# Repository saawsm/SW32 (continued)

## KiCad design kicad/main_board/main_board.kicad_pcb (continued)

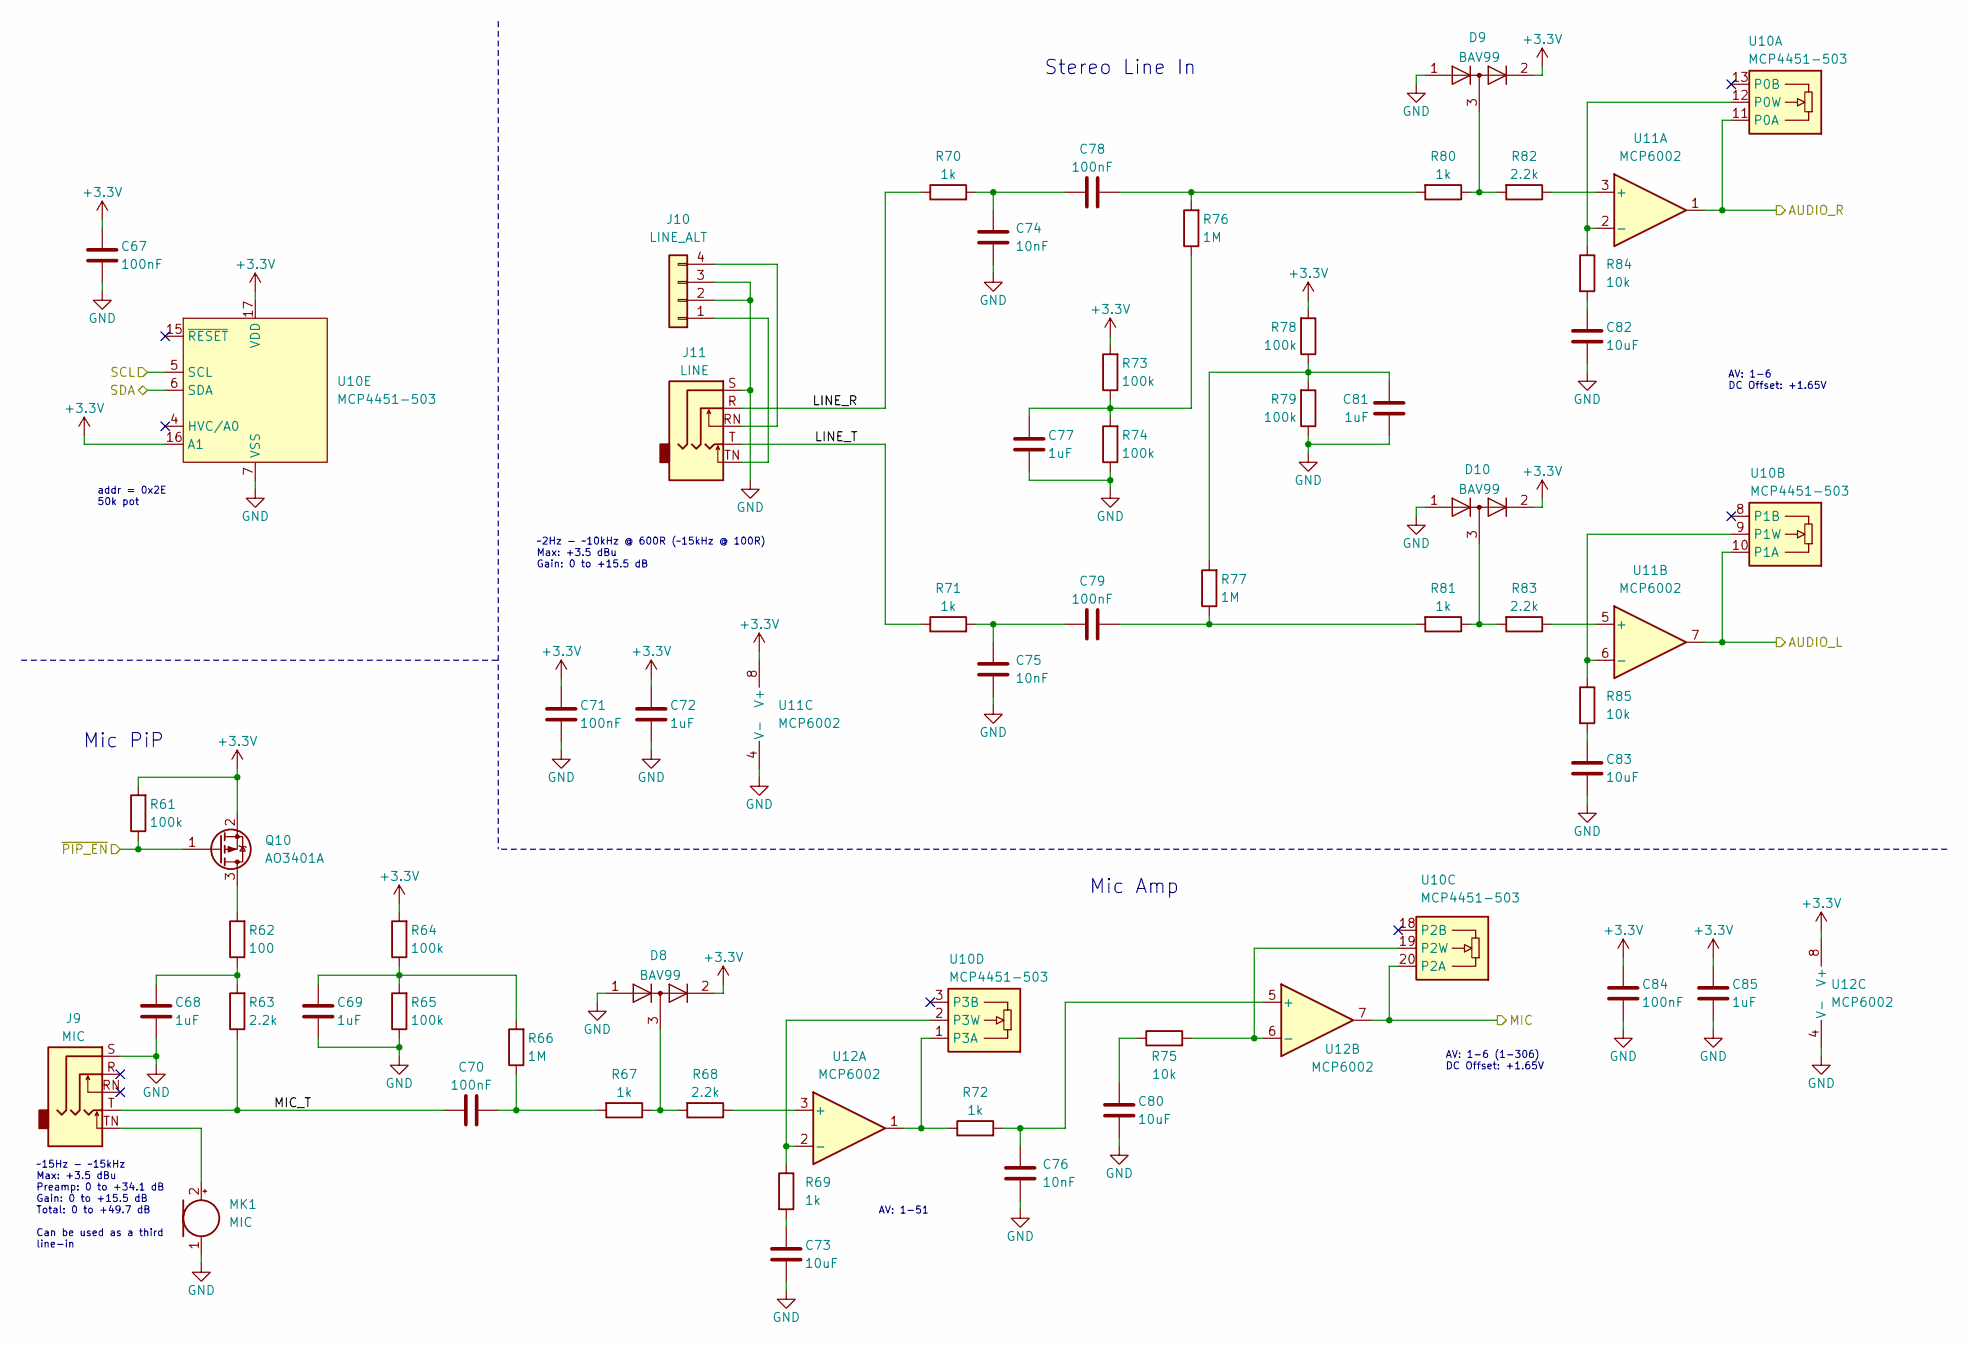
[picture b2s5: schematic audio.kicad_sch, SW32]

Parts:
C67, C70, C71, C78, C79, C84: 100nF; C_0603_1608Metric; LCSC C14663
C68, C69, C72, C77, C81, C85: 1uF; C_0603_1608Metric; LCSC C15849
C73, C80, C82, C83: 10uF; C_0603_1608Metric; LCSC C96446
C74, C75, C76: 10nF; C_0603_1608Metric; LCSC C57112
D8, D9, D10: BAV99; SOT-23; LCSC C2500
J9: MIC; PJ-3062-CO; LCSC C319113
J10: LINE_ALT; PinHeader_1x04_P2.54mm_Vertical; LCSC C2691448
J11: LINE; PJ-3062-CO; LCSC C319113
MK1: MIC; CUI_CMC-4013-SMT; LCSC C5160218
Q10: AO3401A; SOT-23; LCSC C15127
R61, R64, R65, R73, R74, R78, R79: 100k; R_0603_1608Metric; LCSC C25803
R62: 100; R_0603_1608Metric; LCSC C22775
R63, R68, R82, R83: 2.2k; R_0603_1608Metric; LCSC C4190
R66, R76, R77: 1M; R_0603_1608Metric; LCSC C22935
R67, R69, R70, R71, R72, R80, R81: 1k; R_0603_1608Metric; LCSC C21190
R75, R84, R85: 10k; R_0603_1608Metric; LCSC C25804
U10: MCP4451-503; TSSOP-20_4.4x6.5mm_P0.65mm; LCSC C638706
U11, U12: MCP6002; MSOP-8_3x3mm_P0.65mm; LCSC C2652308

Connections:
+3.3V: C67.1, C71.1, C72.1, C84.1, C85.1, D8.2 (A), D9.2 (A), D10.2 (A), Q10.2 (S), R61.2, R64.2, R73.2, R78.2, U10.16 (A1), U10.17 (VDD), U11.8 (V+), U12.8 (V+); also elsewhere on the board
/Audio/AUDIO_L: U10.10 (P1A), U11.7; also elsewhere on the board
/Audio/AUDIO_R: U10.11 (P0A), U11.1; also elsewhere on the board
/Audio/LINE_R: J11.R, R70.1
/Audio/LINE_T: J11.T, R71.1
/Audio/MIC: U10.20 (P2A), U12.7; also elsewhere on the board
/Audio/MIC_T: C70.1, J9.T, R63.1
/Audio/~PIP_EN: Q10.1 (G), R61.1; also elsewhere on the board
/Charger/SCL: U10.5 (SCL); also elsewhere on the board
/Charger/SDA: U10.6 (SDA); also elsewhere on the board
GND: C67.2, C68.2, C69.2, C71.2, C72.2, C73.2, C74.2, C75.2, C76.2, C77.2, C80.2, C81.2, C82.2, C83.2, C84.2, C85.2, D8.1 (K), D9.1 (K), D10.1 (K), J9.S, J10.2, J10.3, J11.S, MK1.1 (-), R65.1, R74.1, R79.1, U10.7 (VSS), U11.4 (V-), U12.4 (V-); also elsewhere on the board
unnamed: C68.1, R62.1, R63.2
unnamed: C69.1, R64.1, R65.2, R66.2
unnamed: C70.2, R66.1, R67.2
unnamed: C73.1, R69.2
unnamed: C74.1, C78.1, R70.2
unnamed: C75.1, C79.1, R71.2
unnamed: C77.1, R73.1, R74.2, R76.1
unnamed: C78.2, R76.2, R80.2
unnamed: C79.2, R77.1, R81.2
unnamed: C80.1, R75.1
unnamed: C81.1, R77.2, R78.1, R79.2
unnamed: C82.1, R84.2
unnamed: C83.1, R85.2
unnamed: D8.3 (K), R67.1, R68.2
unnamed: D9.3 (K), R80.1, R82.2
unnamed: D10.3 (K), R81.1, R83.2
unnamed: J10.1, J11.TN
unnamed: J10.4, J11.RN
unnamed: J9.TN, MK1.2 (+)
unnamed: Q10.3 (D), R62.2
unnamed: R84.1, U10.12 (P0W), U11.2 (-)
unnamed: R85.1, U10.9 (P1W), U11.6 (-)
unnamed: R75.2, U10.19 (P2W), U12.6 (-)
unnamed: R72.1, U10.1 (P3A), U12.1
unnamed: R69.1, U10.2 (P3W), U12.2 (-)
unnamed: R82.1, U11.3 (+)
unnamed: R83.1, U11.5 (+)
unnamed: R68.1, U12.3 (+)
unnamed: C76.1, R72.2, U12.5 (+)

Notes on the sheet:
AV: 1-6 (1-306) DC Offset: +1.65V
Mic PiP
Stereo Line In
~2Hz - ~10kHz @ 600R (~15kHz @ 100R) Max: +3.5 dBu Gain: 0 to +15.5 dB
addr = 0x2E 50k pot
Mic Amp
~15Hz - ~15kHz Max: +3.5 dBu Preamp: 0 to +34.1 dB Gain: 0 to +15.5 dB Total: 0 to +49.7 dB Can be used as a third line-in
AV: 1-51
AV: 1-6 DC Offset: +1.65V

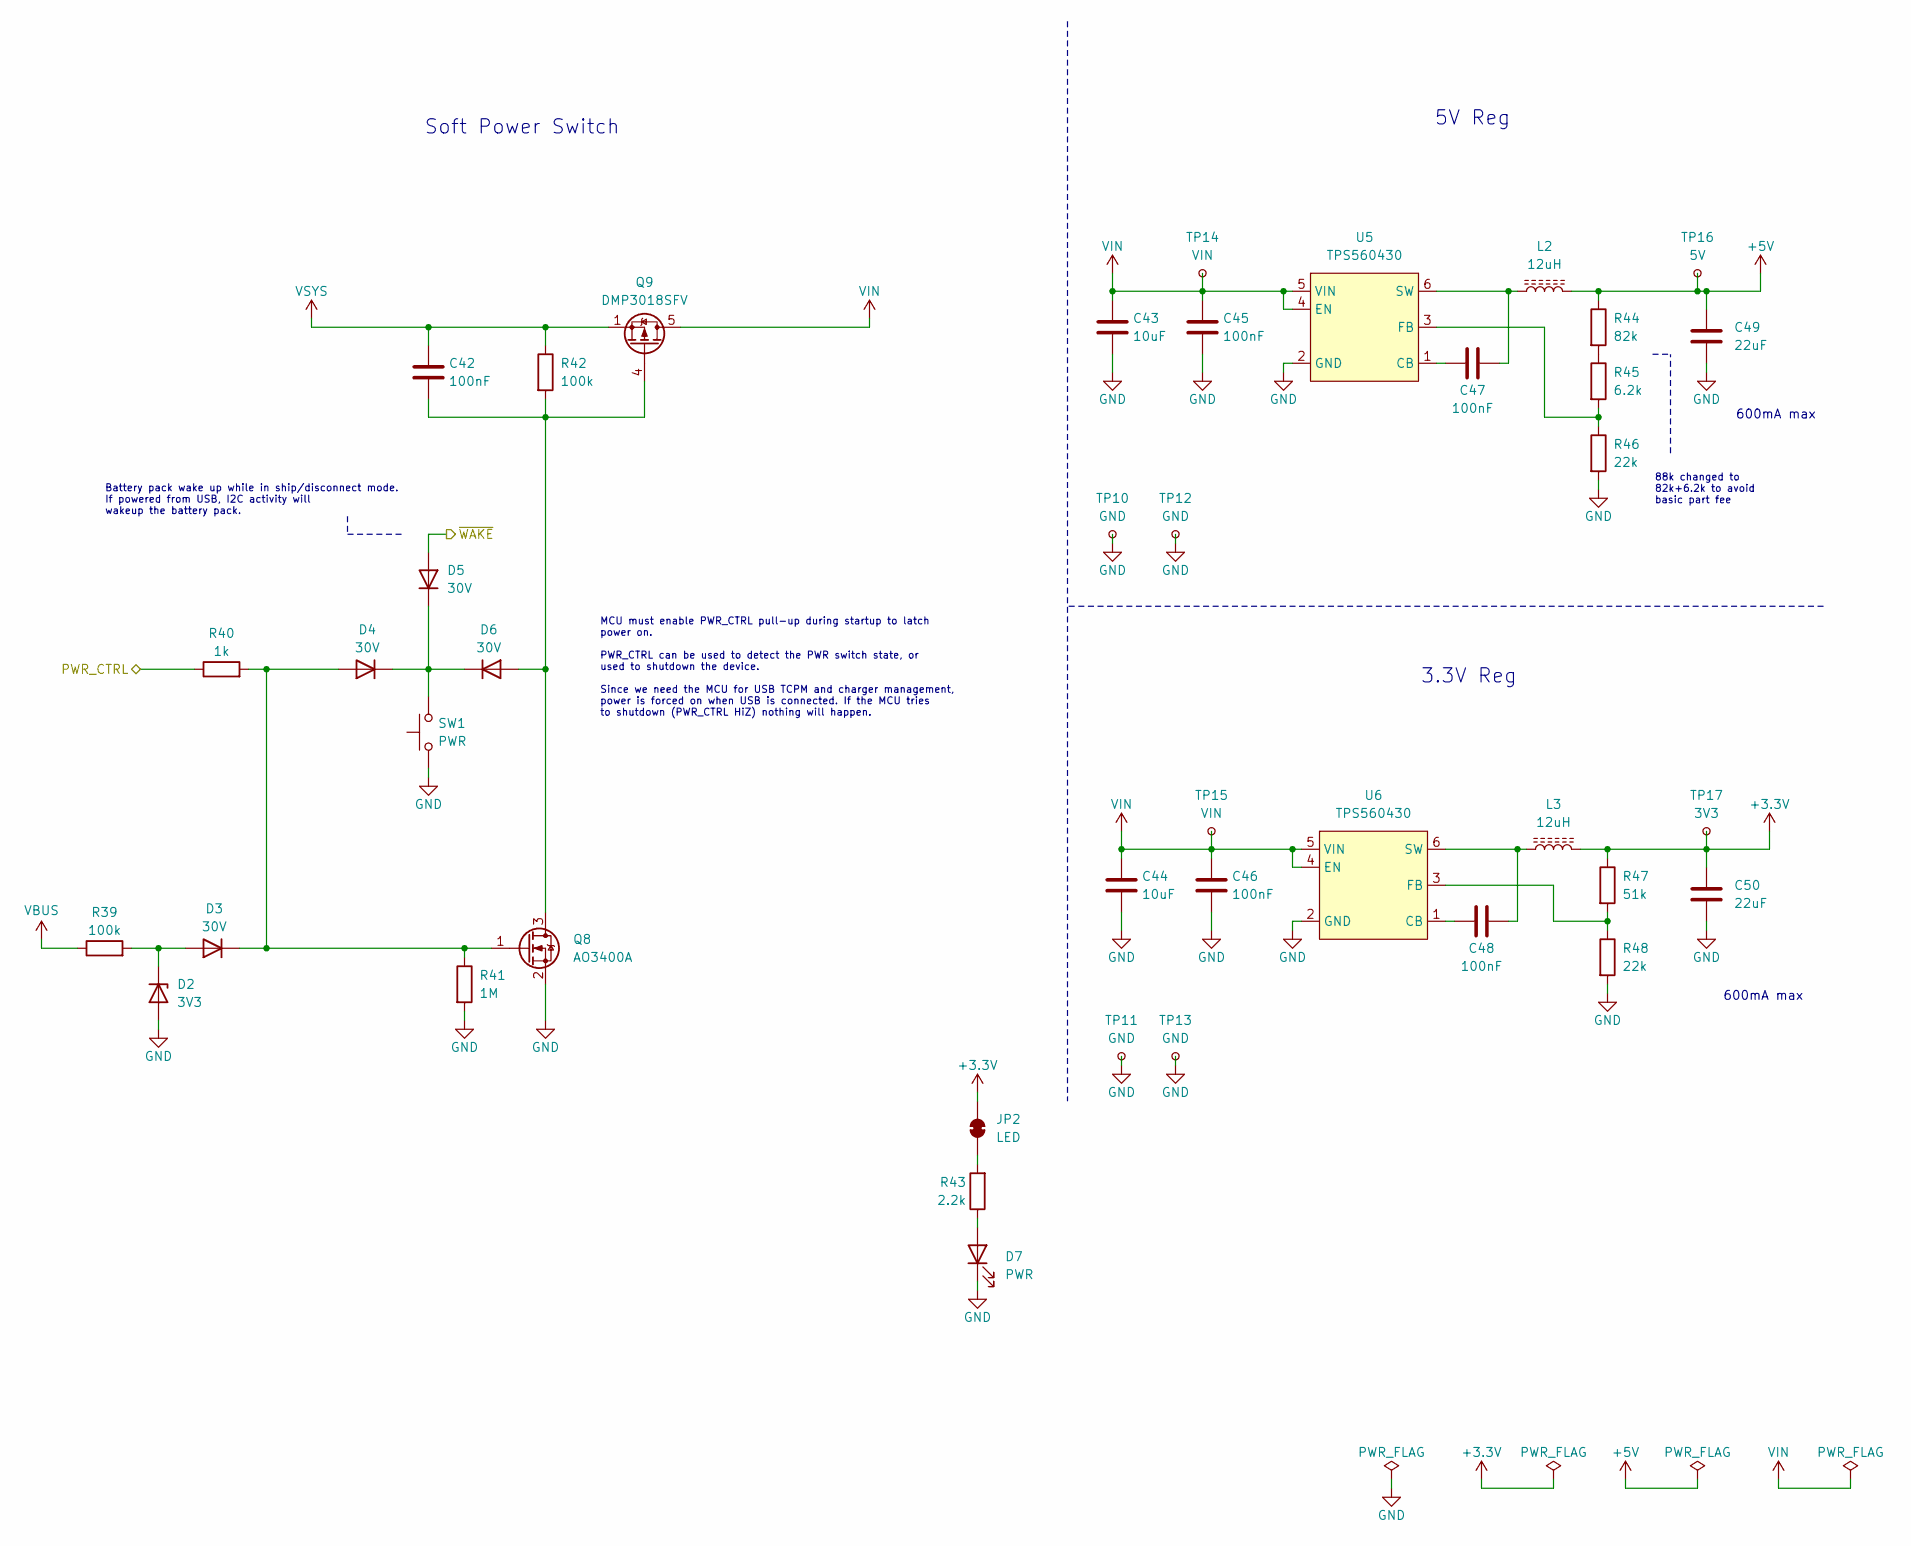
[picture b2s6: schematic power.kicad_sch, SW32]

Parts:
C42, C45, C46, C47, C48: 100nF; C_0603_1608Metric; LCSC C14663
C43, C44: 10uF; C_0805_2012Metric; LCSC C440198
C49, C50: 22uF; C_0805_2012Metric; LCSC C45783
D2: 3V3; D_SOD-323; LCSC C391441
D3, D4, D5, D6: 30V; D_SOD-323; LCSC C2128
D7: PWR; LED_0603_1608Metric; LCSC C2286
JP2: LED; SolderJumper-2_P1.3mm_Bridged_RoundedPad1.0x1.5mm
L2, L3: 12uH; L_Sunlord_SWPA6020S; LCSC C96927
Q8: AO3400A; SOT-23; LCSC C20917
Q9: DMP3018SFV; Diodes_PowerDI3333-8_ThermalVias; LCSC C461075
R39, R42: 100k; R_0603_1608Metric; LCSC C25803
R40: 1k; R_0603_1608Metric; LCSC C21190
R41: 1M; R_0603_1608Metric; LCSC C22935
R43: 2.2k; R_0603_1608Metric; LCSC C4190
R44: 82k; R_0603_1608Metric; LCSC C23254
R45: 6.2k; R_0603_1608Metric; LCSC C4260
R46, R48: 22k; R_0603_1608Metric; LCSC C31850
R47: 51k; R_0603_1608Metric; LCSC C23196
SW1: PWR; SW_Tactile_SPST_Angled_PTS645Vx31-2LFS; LCSC C2804591
TP10, TP11, TP12, TP13: GND; TestPoint_Pad_D1.0mm
TP14, TP15: VIN; TestPoint_Pad_D1.0mm
TP16: 5V; TestPoint_Pad_D1.0mm
TP17: 3V3; TestPoint_Pad_D1.0mm
U5, U6: TPS560430; SOT-23-6; LCSC C524782

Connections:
+3.3V: C50.2, JP2.1 (A), L3.2, R47.1, TP17.1; also elsewhere on the board
+5V: C49.2, L2.2, R44.1, TP16.1; also elsewhere on the board
/Charger/~WAKE: D5.2 (A); also elsewhere on the board
/Controller/PWR_CTRL: R40.1; also elsewhere on the board
GND: C43.1, C44.1, C45.1, C46.1, C49.1, C50.1, D2.2 (A), D7.1 (K), Q8.2 (S), R41.2, R46.2, R48.2, SW1.1, TP10.1, TP11.1, TP12.1, TP13.1, U5.2 (GND), U6.2 (GND); also elsewhere on the board
unnamed: D2.1 (K), D3.2 (A), R39.2
unnamed: D3.1 (K), D4.2 (A), Q8.1 (G), R40.2, R41.1
unnamed: D4.1 (K), D5.1 (K), D6.1 (K), SW1.2
unnamed: C42.1, D6.2 (A), Q8.3 (D), Q9.4 (G), R42.2
unnamed: D7.2 (A), R43.1
unnamed: JP2.2 (B), R43.2
unnamed: R44.2, R45.1
unnamed: C47.1, U5.1 (CB)
unnamed: R45.2, R46.1, U5.3 (FB)
unnamed: C47.2, L2.1, U5.6 (SW)
unnamed: C48.1, U6.1 (CB)
unnamed: R47.2, R48.1, U6.3 (FB)
unnamed: C48.2, L3.1, U6.6 (SW)
VBUS: R39.1; also elsewhere on the board
VIN: C43.2, C44.2, C45.2, C46.2, Q9.5 (D), TP14.1, TP15.1, U5.4 (EN), U5.5 (VIN), U6.4 (EN), U6.5 (VIN); also elsewhere on the board
VSYS: C42.2, Q9.1 (S), Q9.2 (S), Q9.3 (S), R42.1; also elsewhere on the board

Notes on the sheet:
88k changed to 82k+6.2k to avoid basic part fee
600mA max
5V Reg
3.3V Reg
Soft Power Switch
Battery pack wake up while in ship/disconnect mode. If powered from USB, I2C activity will wakeup the battery pack.
MCU must enable PWR_CTRL pull-up during startup to latch power on. PWR_CTRL can be used to detect the PWR switch state, or used to shutdown the device. Since we need the MCU for USB TCPM and charger management, power is forced on when USB is connected. If the MCU tries to shutdown (PWR_CTRL HiZ) no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

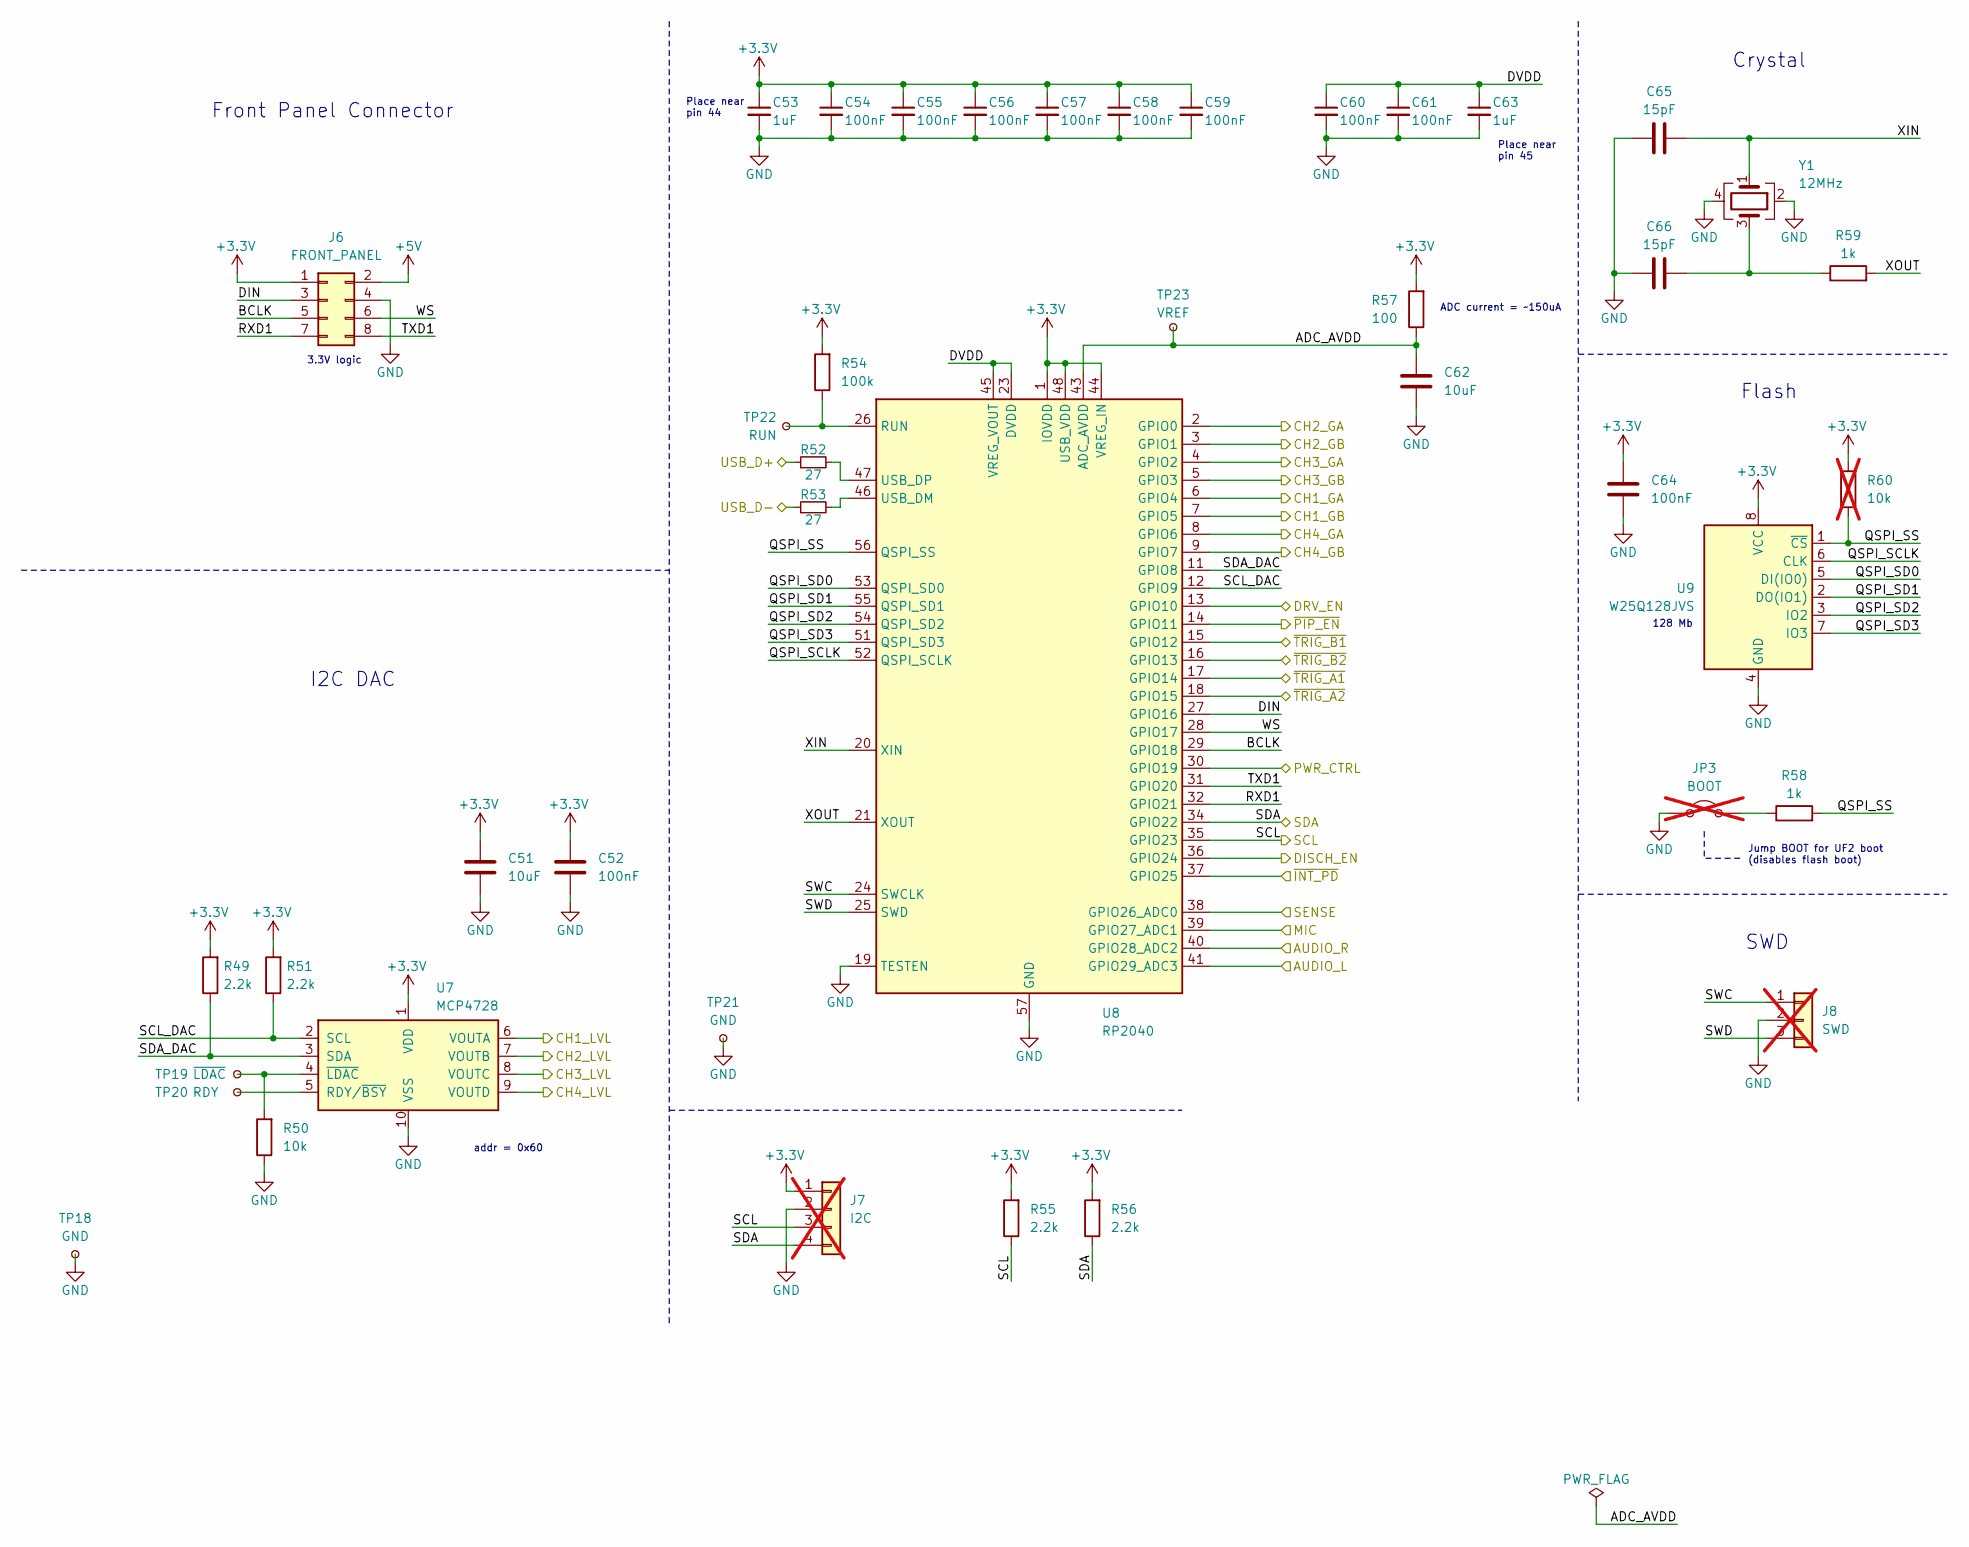
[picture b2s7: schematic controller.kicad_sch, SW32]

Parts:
C51, C62: 10uF; C_0603_1608Metric; LCSC C96446
C52, C64: 100nF; C_0603_1608Metric; LCSC C14663
C53, C63: 1uF; C_0603_1608Metric; LCSC C15849
C54, C55, C56, C57, C58, C59, C60, C61: 100nF; C_0402_1005Metric; LCSC C307331
C65, C66: 15pF; C_0402_1005Metric; LCSC C1548
J6: FRONT_PANEL; IDC-Header_2x04_P2.54mm_Vertical; LCSC C5372864
J7: I2C; PinHeader_1x04_P2.54mm_Vertical; LCSC C2691448; not fitted
J8: SWD; PinHeader_1x03_P2.54mm_Vertical; LCSC C2937625; not fitted
JP3: BOOT; PinHeader_1x02_P2.54mm_Vertical; LCSC C492401; not fitted
R49, R51, R55, R56: 2.2k; R_0603_1608Metric; LCSC C4190
R50: 10k; R_0603_1608Metric; LCSC C25804
R52, R53: 27; R_0402_1005Metric; LCSC C25100
R54: 100k; R_0603_1608Metric; LCSC C25803
R57: 100; R_0603_1608Metric; LCSC C22775
R58: 1k; R_0603_1608Metric; LCSC C21190
R59: 1k; R_0402_1005Metric; LCSC C11702
R60: 10k; R_0603_1608Metric; LCSC C25804; not fitted
TP18, TP21: GND; TestPoint_Pad_D1.0mm
TP19: ~{LDAC}; TestPoint_Pad_D1.0mm
TP20: RDY; TestPoint_Pad_D1.0mm
TP22: RUN; TestPoint_Pad_D1.0mm
TP23: VREF; TestPoint_Pad_D1.0mm
U7: MCP4728; MSOP-10_3x3mm_P0.5mm; LCSC C108207
U8: RP2040; QFN-56-1EP_7x7mm_P0.4mm_EP3.2x3.2mm_ThermalVias; LCSC C2040
U9: W25Q128JVS; SOIC-8_5.23x5.23mm_P1.27mm; LCSC C97521
Y1: 12MHz; Crystal_SMD_3225-4Pin_3.2x2.5mm; LCSC C20625731

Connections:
+3.3V: C51.1, C52.1, C53.1, C54.1, C55.1, C56.1, C57.1, C58.1, C59.1, C64.1, J6.1, J7.1, R49.2, R51.2, R54.2, R55.2, R56.2, R57.2, R60.2, U7.1 (VDD), U8.1 (IOVDD), U8.10 (IOVDD), U8.22 (IOVDD), U8.33 (IOVDD), U8.42 (IOVDD), U8.44 (VREG_IN), U8.48 (USB_VDD), U8.49 (IOVDD), U9.8 (VCC); also elsewhere on the board
+5V: J6.2; also elsewhere on the board
/Audio/AUDIO_L: U8.41 (GPIO29_ADC3); also elsewhere on the board
/Audio/AUDIO_R: U8.40 (GPIO28_ADC2); also elsewhere on the board
/Audio/MIC: U8.39 (GPIO27_ADC1); also elsewhere on the board
/Audio/~PIP_EN: U8.14 (GPIO11); also elsewhere on the board
/Charger/SCL: J7.3, R55.1, U8.35 (GPIO23); also elsewhere on the board
/Charger/SDA: J7.4, R56.1, U8.34 (GPIO22); also elsewhere on the board
/Controller/ADC_AVDD: C62.1, R57.1, TP23.1, U8.43 (ADC_AVDD)
/Controller/BCLK: J6.5, U8.29 (GPIO18)
/Controller/CH1_GA: U8.6 (GPIO4); also elsewhere on the board
/Controller/CH1_GB: U8.7 (GPIO5); also elsewhere on the board
/Controller/CH1_LVL: U7.6 (VOUTA); also elsewhere on the board
/Controller/CH2_GA: U8.2 (GPIO0); also elsewhere on the board
/Controller/CH2_GB: U8.3 (GPIO1); also elsewhere on the board
/Controller/CH2_LVL: U7.7 (VOUTB); also elsewhere on the board
/Controller/CH3_GA: U8.4 (GPIO2); also elsewhere on the board
/Controller/CH3_GB: U8.5 (GPIO3); also elsewhere on the board
/Controller/CH3_LVL: U7.8 (VOUTC); also elsewhere on the board
/Controller/CH4_GA: U8.8 (GPIO6); also elsewhere on the board
/Controller/CH4_GB: U8.9 (GPIO7); also elsewhere on the board
/Controller/CH4_LVL: U7.9 (VOUTD); also elsewhere on the board
/Controller/DIN: J6.3, U8.27 (GPIO16)
/Controller/DISCH_EN: U8.36 (GPIO24); also elsewhere on the board
/Controller/DRV_EN: U8.13 (GPIO10); also elsewhere on the board
/Controller/DVDD: C60.1, C61.1, C63.1, U8.23 (DVDD), U8.45 (VREG_VOUT), U8.50 (DVDD)
/Controller/PWR_CTRL: U8.30 (GPIO19); also elsewhere on the board
/Controller/QSPI_SCLK: U8.52 (QSPI_SCLK), U9.6 (CLK)
/Controller/QSPI_SD0: U8.53 (QSPI_SD0), U9.5 (DI(IO0))
/Controller/QSPI_SD1: U8.55 (QSPI_SD1), U9.2 (DO(IO1))
/Controller/QSPI_SD2: U8.54 (QSPI_SD2), U9.3 (IO2)
/Controller/QSPI_SD3: U8.51 (QSPI_SD3), U9.7 (IO3)
/Controller/QSPI_SS: R58.2, R60.1, U8.56 (QSPI_SS), U9.1 (~CS)
/Controller/RXD1: J6.7, U8.32 (GPIO21)
/Controller/SCL_DAC: R51.1, U7.2 (SCL), U8.12 (GPIO9)
/Controller/SDA_DAC: R49.1, U7.3 (SDA), U8.11 (GPIO8)
/Controller/SENSE: U8.38 (GPIO26_ADC0); also elsewhere on the board
/Controller/SWC: J8.1, U8.24 (SWCLK)
/Controller/SWD: J8.3, U8.25 (SWD)
/Controller/TXD1: J6.8, U8.31 (GPIO20)
/Controller/WS: J6.6, U8.28 (GPIO17)
/Controller/XIN: C65.2, U8.20 (XIN), Y1.1
/Controller/XOUT: R59.2, U8.21 (XOUT)
/Controller/~INT_PD: U8.37 (GPIO25); also elsewhere on the board
/Controller/~TRIG_A1: U8.17 (GPIO14); also elsewhere on the board
/Controller/~TRIG_A2: U8.18 (GPIO15); also elsewhere on the board
/Controller/~TRIG_B1: U8.15 (GPIO12); also elsewhere on the board
/Controller/~TRIG_B2: U8.16 (GPIO13); also elsewhere on the board
/Input/USB_D+: R52.1; also elsewhere on the board
/Input/USB_D-: R53.1; also elsewhere on the board
GND: C51.2, C52.2, C53.2, C54.2, C55.2, C56.2, C57.2, C58.2, C59.2, C60.2, C61.2, C62.2, C63.2, C64.2, C65.1, C66.1, J6.4, J7.2, J8.2, JP3.1 (A), R50.1, TP18.1, TP21.1, U7.10 (VSS), U8.19 (TESTEN), U8.57 (GND), U9.4 (GND), Y1.2, Y1.4; also elsewhere on the board
unnamed: C66.2, R59.1, Y1.3
unnamed: JP3.2 (B), R58.1
unnamed: TP20.1, U7.5 (RDY/~BSY)
unnamed: R50.2, TP19.1, U7.4 (~LDAC)
unnamed: R54.1, TP22.1, U8.26 (RUN)
unnamed: R53.2, U8.46 (USB_DM)
unnamed: R52.2, U8.47 (USB_DP)

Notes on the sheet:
Crystal
Jump BOOT for UF2 boot (disables flash boot)
addr = 0x60
SWD
ADC current = ~150uA
3.3V logic
Front Panel Connector
I2C DAC
Place near pin 44
Place near pin 45
Flash
128 Mb

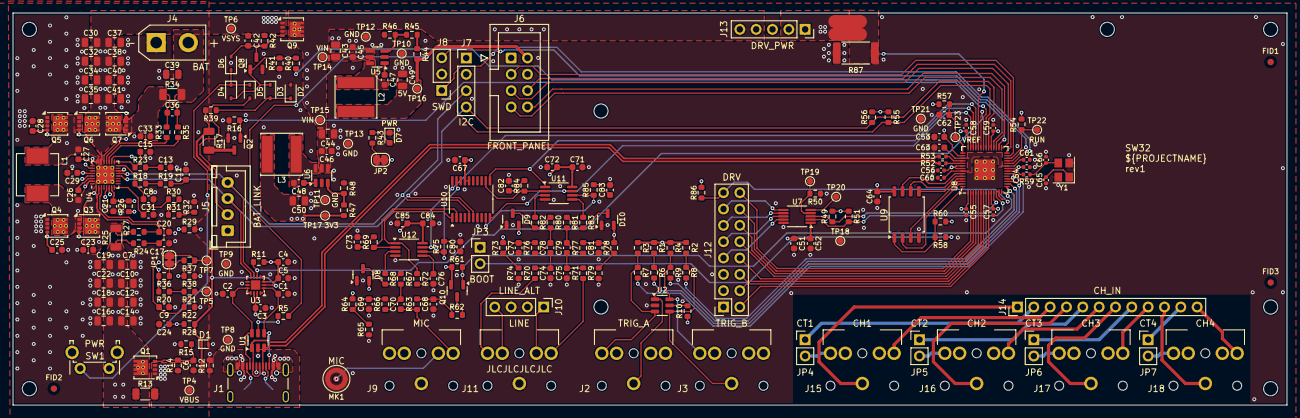
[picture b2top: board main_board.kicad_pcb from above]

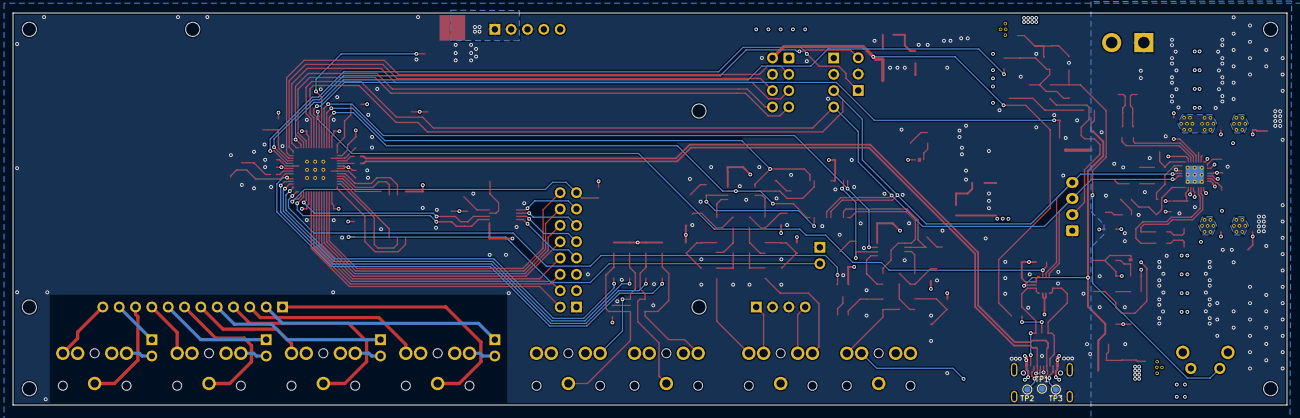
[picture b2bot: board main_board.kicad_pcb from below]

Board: 4 copper layers, 198.1 x 61.0 mm, 271 parts (3 on the bottom side), 169 nets.

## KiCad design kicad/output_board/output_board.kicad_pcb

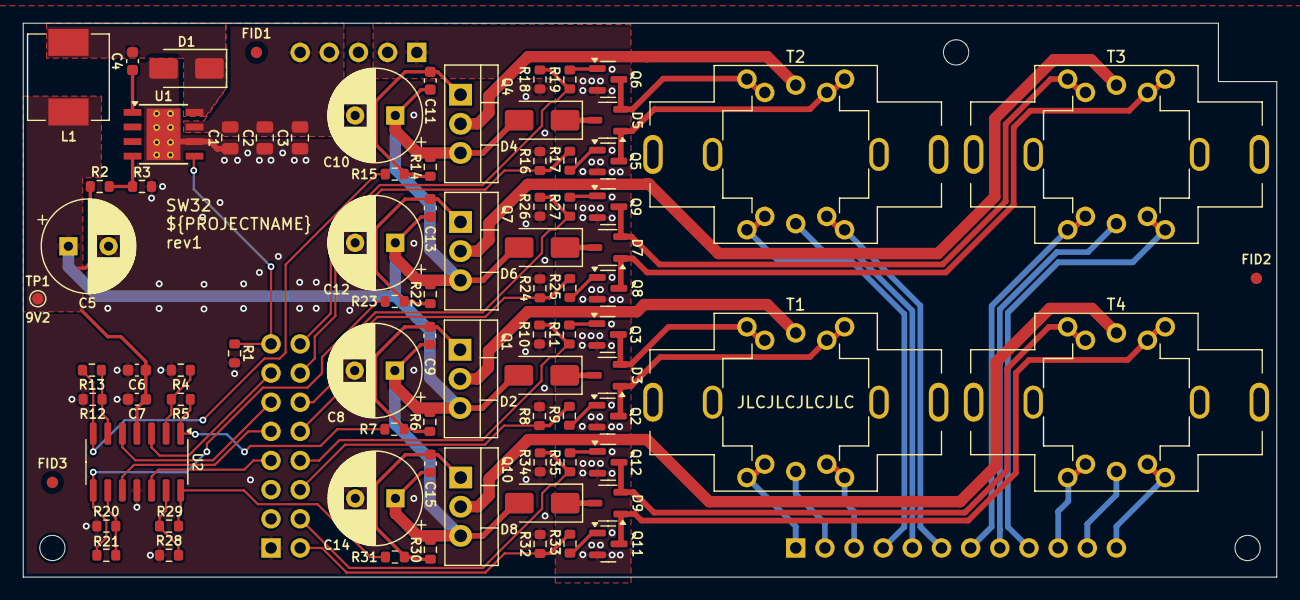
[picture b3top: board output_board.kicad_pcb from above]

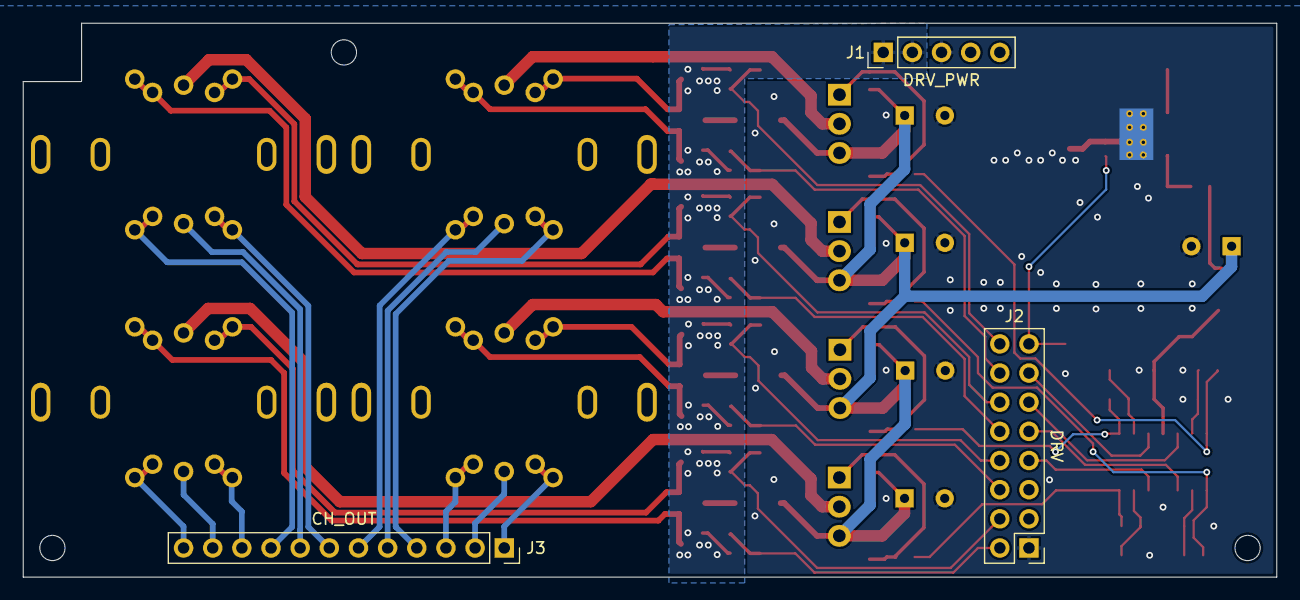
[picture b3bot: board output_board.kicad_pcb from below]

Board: 2 copper layers, 109.2 x 48.3 mm, 88 parts (3 on the bottom side), 68 nets.

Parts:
C1, C2, C3: 22uF; C_0805_2012Metric
C4: 10nF; C_0603_1608Metric
C5, C8, C10, C12, C14: 220uF; CP_Radial_D8.0mm_P3.50mm
C6: 1uF; C_0603_1608Metric
C7, C9, C11, C13, C15: 100nF; C_0603_1608Metric
D1: SS34; D_SMA
D2, D4, D6, D8: SMAJ13A; D_SMA
D3, D5, D7, D9: BAV23CL; SOT-23-3
FID1, FID2, FID3: Fiducial; Fiducial_1mm_Mask2mm
H1, H2, H3: MountingHole; MountingHole_2.2mm_M2
J1: DRV_PWR; PinHeader_1x05_P2.54mm_Vertical
J2: DRV; PinHeader_2x08_P2.54mm_Vertical
J3: CH_OUT; PinSocket_1x12_P2.54mm_Vertical
L1: 15uH; L_CJIANG_FXL0630
Q1, Q4, Q7, Q10: IRF9Z24NPBF; TO-220-3_Vertical
Q2, Q3, Q5, Q6, Q8, Q9, Q11, Q12: AO3400A; SOT-23
R1, R8, R10, R16, R18, R24, R26, R32, R34: 100k; R_0603_1608Metric
R2, R4, R5, R12, R13, R20, R21, R28, R29: 10k; R_0603_1608Metric
R3: 1.5k; R_0603_1608Metric
R6, R14, R22, R30: 2k; R_0603_1608Metric
R7, R15, R23, R31: 1k; R_0603_1608Metric
R9, R11, R17, R19, R25, R27, R33, R35: 100; R_0603_1608Metric
T1, T2, T3, T4: 42TL004/42TU200; 42TL_TU
TP1: 9V2; TestPoint_Pad_D1.0mm
U1: TPS5430DDA; TI_SO-PowerPAD-8_ThermalVias
U2: LM324DT; SOIC-14_3.9x8.7mm_P1.27mm

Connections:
+9V: C5.1, C6.1, C7.1, C8.1, C9.1, C10.1, C11.1, C12.1, C13.1, C14.1, C15.1, D2.2 (A2), D4.2 (A2), D6.2 (A2), D8.2 (A2), L1.2, Q1.3 (S), Q4.3 (S), Q7.3 (S), Q10.3 (S), R2.2, R6.2, R14.2, R22.2, R30.2, TP1.1, U2.4 (V+)
/CH1_GA: J2.8, R10.1, R11.1
/CH1_GB: J2.6, R8.1, R9.1
/CH1_LVL: J2.13, U2.3 (+)
/CH2_GA: J2.16, R18.1, R19.1
/CH2_GB: J2.14, R16.1, R17.1
/CH2_LVL: J2.11, U2.5 (+)
/CH3_GA: J2.12, R26.1, R27.1
/CH3_GB: J2.10, R24.1, R25.1
/CH3_LVL: J2.9, U2.10 (+)
/CH4_GA: J2.4, R34.1, R35.1
/CH4_GB: J2.2, R32.1, R33.1
/CH4_LVL: J2.7, U2.12 (+)
/Channel 1/OUTA: J3.1, T1.4 (S1)
/Channel 1/OUTB: J3.3, T1.6 (S2)
/Channel 1/OUTM: J3.2, T1.5 (SM)
/Channel 2/OUTA: J3.4, T2.4 (S1)
/Channel 2/OUTB: J3.6, T2.6 (S2)
/Channel 2/OUTM: J3.5, T2.5 (SM)
/Channel 3/OUTA: J3.7, T3.4 (S1)
/Channel 3/OUTB: J3.9, T3.6 (S2)
/Channel 3/OUTM: J3.8, T3.5 (SM)
/Channel 4/OUTA: J3.10, T4.4 (S1)
/Channel 4/OUTB: J3.12, T4.6 (S2)
/Channel 4/OUTM: J3.11, T4.5 (SM)
/DRV_EN: J2.15, R1.1, U1.5 (EN)
/PGND: J1.1, J1.2, Q2.2 (S), Q3.2 (S), Q5.2 (S), Q6.2 (S), Q8.2 (S), Q9.2 (S), Q11.2 (S), Q12.2 (S)
GND: C1.1, C2.1, C3.1, C5.2, C6.2, C7.2, C8.2, C10.2, C12.2, C14.2, D1.2 (A), J1.3, J2.1, R1.2, R3.2, R4.1, R8.2, R10.2, R12.1, R16.2, R18.2, R20.1, R24.2, R26.2, R28.1, R32.2, R34.2, U1.6 (GND), U1.9 (GNDPAD), U2.11 (V-)
unnamed: C4.2, D1.1 (K), L1.1, U1.8 (PH)
unnamed: D2.1 (A1), D3.3 (K)
unnamed: D3.1 (A), Q2.3 (D), T1.1 (PR1)
unnamed: D4.1 (A1), D5.3 (K)
unnamed: D5.1 (A), Q5.3 (D), T2.1 (PR1)
unnamed: D6.1 (A1), D7.3 (K)
unnamed: D7.1 (A), Q8.3 (D), T3.1 (PR1)
unnamed: D8.1 (A1), D9.3 (K)
unnamed: D9.1 (A), Q11.3 (D), T4.1 (PR1)
unnamed: Q1.2 (D), T1.2 (PM)
unnamed: C9.2, Q1.1 (G), R6.1, R7.2
unnamed: Q2.1 (G), R9.2
unnamed: D3.2 (K), Q3.3 (D), T1.3 (PR2)
unnamed: Q3.1 (G), R11.2
unnamed: Q4.2 (D), T2.2 (PM)
unnamed: C11.2, Q4.1 (G), R14.1, R15.2
unnamed: Q5.1 (G), R17.2
unnamed: D5.2 (K), Q6.3 (D), T2.3 (PR2)
unnamed: Q6.1 (G), R19.2
unnamed: Q7.2 (D), T3.2 (PM)
unnamed: C13.2, Q7.1 (G), R22.1, R23.2
unnamed: Q8.1 (G), R25.2
unnamed: D7.2 (K), Q9.3 (D), T3.3 (PR2)
unnamed: Q9.1 (G), R27.2
unnamed: Q10.2 (D), T4.2 (PM)
unnamed: C15.2, Q10.1 (G), R30.1, R31.2
unnamed: Q11.1 (G), R33.2
unnamed: D9.2 (K), Q12.3 (D), T4.3 (PR2)
unnamed: Q12.1 (G), R35.2
unnamed: R5.1, R7.1, U2.1
unnamed: R13.1, R15.1, U2.7
unnamed: R21.1, R23.1, U2.8
unnamed: R29.1, R31.1, U2.14
unnamed: C4.1, U1.1 (BOOT)
unnamed: R2.1, R3.1, U1.4 (VSENSE)
unnamed: R4.2, R5.2, U2.2 (-)
unnamed: R12.2, R13.2, U2.6 (-)
unnamed: R20.2, R21.2, U2.9 (-)
unnamed: R28.2, R29.2, U2.13 (-)
VIN: C1.2, C2.2, C3.2, J1.4, J1.5, U1.7 (VIN)

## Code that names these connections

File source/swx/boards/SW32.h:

/*
 * swx
 * Copyright (C) 2024 saawsm
 *
 * This program is free software: you can redistribute it and/or modify
 * it under the terms of the GNU General Public License as published by
 * the Free Software Foundation, either version 3 of the License, or
 * (at your option) any later version.
 *
 * This program is distributed in the hope that it will be useful,
 * but WITHOUT ANY WARRANTY; without even the implied warranty of
 * MERCHANTABILITY or FITNESS FOR A PARTICULAR PURPOSE. See the
 * GNU General Public License for more details.
 *
 * You should have received a copy of the GNU General Public License
 * along with this program.  If not, see <http://www.gnu.org/licenses/>.
 */

#ifndef _BOARDS_SW32_H
#define _BOARDS_SW32_H

#define PIN_PWR_CTRL (19)
#define PIN_DRV_EN (10)
#define PIN_PIP_EN (11) // active low
#define PIN_DISCH_EN (24)

#define PIN_INT_PD (25) // active low

// -------- Triggers --------
#define PIN_TRIG_A1 (14) // active low
#define PIN_TRIG_A2 (15) // active low
#define PIN_TRIG_B1 (12) // active low
#define PIN_TRIG_B2 (13) // active low

// -------- I2C --------
#define PIN_I2C_SCL (23)
#define PIN_I2C_SDA (22)
#define I2C_PORT (i2c1)
#define I2C_FREQ (400000) // Hz

#define PIN_I2C_SCL_DAC (9)
#define PIN_I2C_SDA_DAC (8)
#define I2C_PORT_DAC (i2c0)
#define I2C_FREQ_DAC (400000) // Hz

#define I2C_ADDRESS_DAC (0x60)
#define I2C_ADDRESS_POT (0x2F)

// -------- UART --------
#define PIN_TXD1 (20)
#define PIN_RXD1 (21)

#define UART_PORT (uart1)
#define UART_BAUD (115200)

// -------- I2S Audio --------
#define PIN_I2S_DIN (16)
#define PIN_I2S_WS (17)
#define PIN_I2S_BCLK (18)

// -------- ADC --------
#define PIN_ADC_SENSE (26)
#define PIN_ADC_AUDIO_LEFT (29)
#define PIN_ADC_AUDIO_RIGHT (28)
#define PIN_ADC_AUDIO_MIC (27)

// -------- Channels --------

// -------- Channel Defaults --------

#define CH_CAL_THRESHOLD_OK (0.015f)
#define CH_CAL_THRESHOLD_OVER (0.018f)
#define CH_CAL_OFFSET (400)

// -------- Channel 1 --------
#define PIN_CH1_GA (4)
#define PIN_CH1_GB (5)
#define CH1_DAC_CH (0)

// -------- Channel 2 --------
#define PIN_CH2_GA (0)
#define PIN_CH2_GB (1)
#define CH2_DAC_CH (1)

// -------- Channel 3 --------
#define PIN_CH3_GA (2)
#define PIN_CH3_GB (3)
#define CH3_DAC_CH (2)

// -------- Channel 4 --------
#define PIN_CH4_GA (6)
#define PIN_CH4_GB (7)
#define CH4_DAC_CH (3)

// ---------------------------

#define PICO_BOOT_STAGE2_CHOOSE_W25Q080 1

#ifndef PICO_FLASH_SPI_CLKDIV
#define PICO_FLASH_SPI_CLKDIV 2
#endif

// 16M flash
#ifndef PICO_FLASH_SIZE_BYTES
#define PICO_FLASH_SIZE_BYTES (16 * 1024 * 1024)
#endif

// Board has B1 RP2040
#ifndef PICO_RP2040_B0_SUPPORTED
#define PICO_RP2040_B0_SUPPORTED 0
#endif

#endif // _SW32_H

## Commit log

2024-05-21 add license
2024-05-21 add initial kicad projects
2024-05-21 add front panel control
2024-05-22 reorder pins to use IO_MUX SPI
2024-05-22 add controller
2024-05-22 add output
2024-05-22 add power
2024-05-22 add input
2024-05-22 add audio
2024-05-22 add charger
2024-05-22 update project details
2024-05-22 add I2S link
2024-05-23 remove BAT_INT
2024-05-23 fix BAT_LINK pinout for consistency
2024-05-23 remove old part number
2024-05-23 add output board
2024-05-23 setup board stackup
2024-05-23 add JLC design rules
2024-05-23 board outline
2024-05-24 update BOM prioritizing basic parts
2024-05-24 use tactile switches
2024-05-24 include in BOM for DNP items
2024-05-25 add generation script
2024-05-26 sort cleanup files before removing
2024-05-26 exclude full board bom in BOMs zip
2024-05-26 add psu
2024-05-26 use same inductor value for both supply rails
2024-05-26 fix missing bom item
2024-05-26 fix invalid bom number
2024-05-26 update bom
2024-05-27 add board setup
2024-05-27 add front panel
2024-05-27 add capacitors
2024-05-27 add inductor footprint
2024-05-27 use SWPA6020S inductor
2024-05-27 layout front panel connectors
2024-05-27 add board config
2024-05-27 add VBUS tvs
2024-05-27 update smd mic bom
2024-05-27 update LED part number
2024-05-28 remove port expander
2024-05-28 fix connectors not in BOM
2024-05-28 add mic footprint
2024-05-28 add status led for USB connector
2024-05-29 use 2x4 IDC connector
2024-05-29 support flashing from main board
2024-05-30 add draft front control board pcb
2024-05-30 fix dru
2024-05-30 add csv extension to pos file
2024-05-30 ignore extracted csv files
2024-05-30 cleanup
2024-05-31 connect charger VBUS before inrush limiter
2024-05-31 use 2x8 pin header
2024-05-31 update buzzer datasheet
2024-06-01 add draft output board
2024-06-01 add silkscreen board info
2024-06-01 cleanup fab layer
2024-06-02 add standoff holes for output board
2024-06-02 add firmware project structure
2024-06-04 ground TESTEN pin
2024-06-04 use SOIC package
2024-06-07 increase 42TU clearance
2024-06-07 move ground to center pin
2024-06-07 add dimensions
2024-06-09 add mainboard pcb
2024-06-09 unify via sizes
2024-06-09 auto detect inner pcb layers
2024-06-10 remove 0.2mm vias
2024-06-10 use thermal via footprints
2024-06-11 fix LED order
2024-06-11 fix missing mosfet 3D models
2024-06-11 update info
2024-06-11 add box name
2024-06-12 fix title block
2024-06-12 adjust USB hole position
2024-06-12 add schematics
2024-06-12 add plot settings
2024-06-12 add ibom config
2024-06-12 set default pos export path
2024-06-12 ignore raw gerber files
2024-06-12 move to source folder
2024-06-13 fix cpl rotations
2024-06-13 add pcbs
2024-06-13 update build info
2024-06-15 fix digipot rotation
2024-06-16 add mkdocs
2024-06-16 add swef submodules
2024-06-16 use c
2024-06-16 add web server setup
2024-06-16 add basic function test
2024-06-16 add doc about firmware
2024-06-16 allow code block copy to clipboard
2024-06-19 add missing vias
2024-06-19 add layer sequence
2024-06-20 fix thermal relief type
2024-06-22 add freertos
2024-06-22 add sdk import script
2024-06-22 add libfixmath
2024-06-22 add lua v5.4.6
2024-06-22 add common headers
2024-06-22 add version string
2024-06-22 add board def
2024-06-22 add thread safe i2c
2024-06-22 remove data partition
2024-06-22 increase spiffs obj name length
2024-06-22 refactor defines
2024-06-22 add input system
2024-06-24 remove freertos
2024-06-26 add output system
2024-06-29 use timestamp pulse gen
2024-07-06 add battery connector part number
2024-07-06 refactor function names
2024-07-06 use adc_read() for output calibration
2024-07-07 add protocol
2024-07-08 add littlefs
2024-07-08 add button_cap model
2024-07-09 use lua float
2024-07-10 add audio processing
2024-07-11 use LFS_THREADSAFE
2024-07-11 add assembly guide
2024-08-11 cmake 3.25
2024-08-11 use lua v5.3.6
2024-08-11 fix crash when accessing flash during fs operation
2024-08-11 add custom panic() handler
2024-08-11 refactor enums
2024-08-11 fix calibration thresholds
2024-08-11 refactor output
2024-08-12 refactor protocol
2024-08-12 add build warnings
2024-09-09 add pulse gen
2024-09-10 add digipot
2024-09-10 add disclaimer
2024-09-10 use actual frequency
2024-09-11 invert default trigger states
2024-09-11 fix power parameter default
2024-09-11 reset stats before calculating
2024-09-11 use per channel pulse queues
2024-09-11 fix sample count
2024-09-11 fix link
2024-09-15 fix gain
2024-09-15 add gain to protocol
2024-09-15 use error state instead of panic()
2024-09-15 read protect parameters if readonly flag set
2024-09-15 refactor calibration
2024-09-15 fix output board detection
2024-09-15 Deployed 0089bb7 with MkDocs version: 1.6.0
